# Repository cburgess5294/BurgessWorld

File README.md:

# BurgessWorld
A repository for documents related to BurgessWorld Custom Electronics Projects

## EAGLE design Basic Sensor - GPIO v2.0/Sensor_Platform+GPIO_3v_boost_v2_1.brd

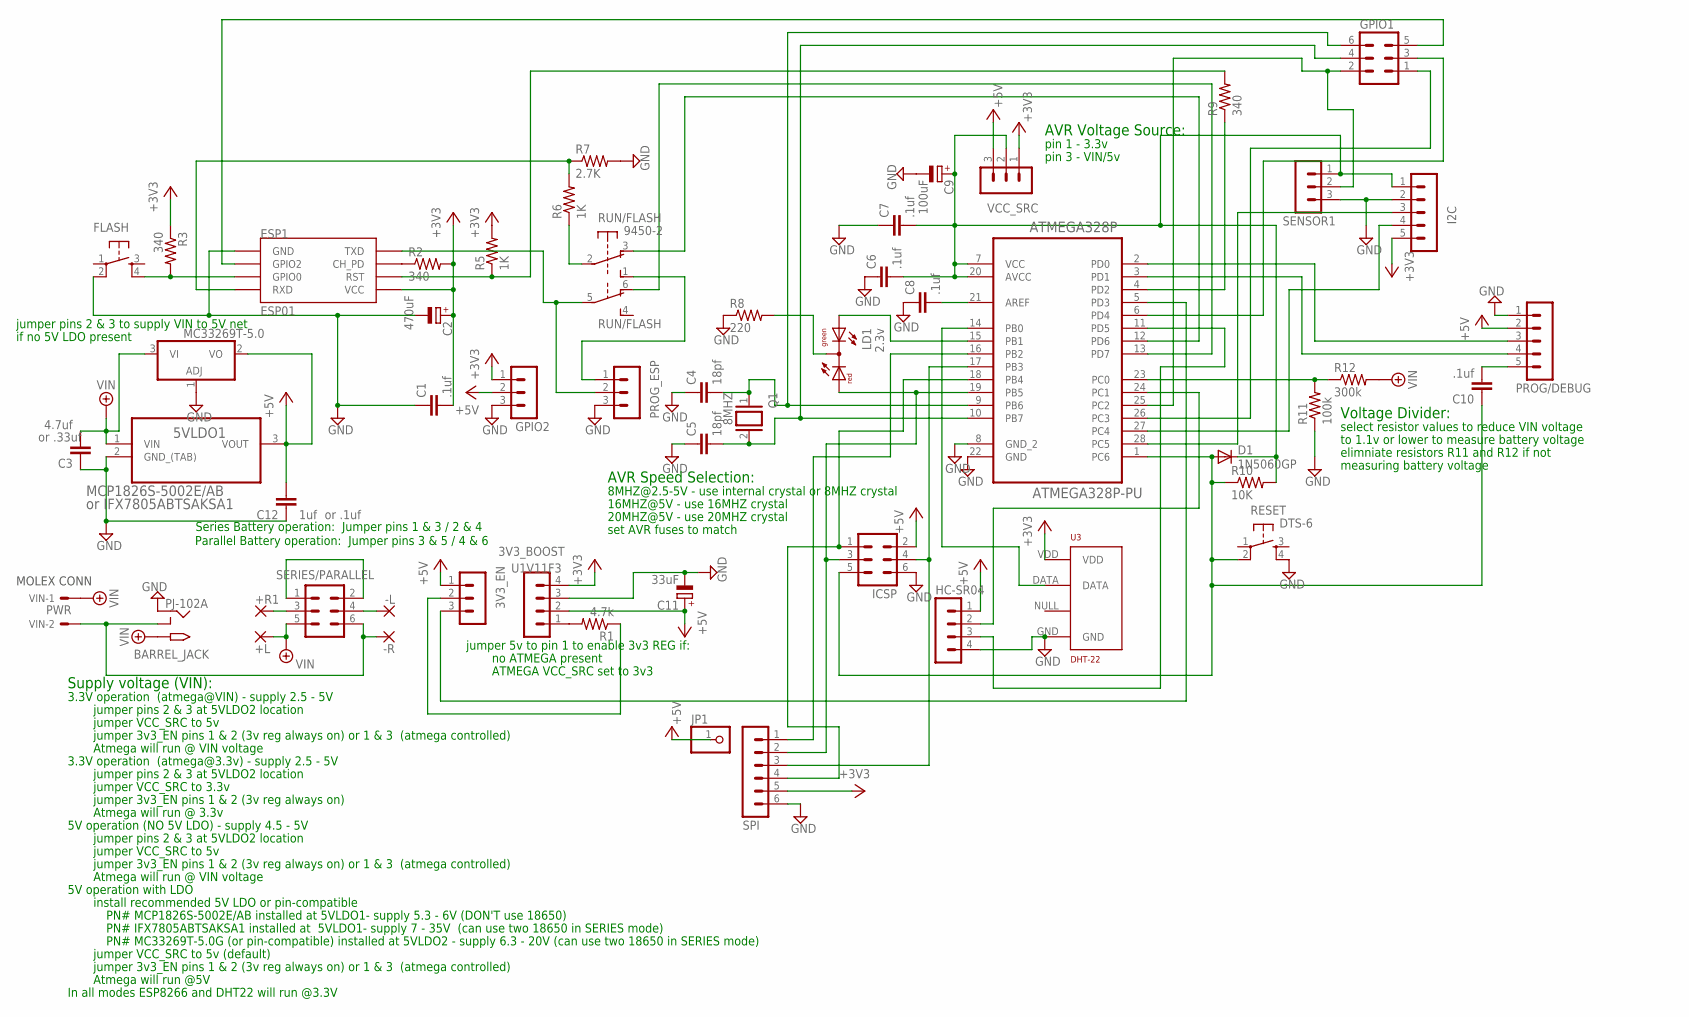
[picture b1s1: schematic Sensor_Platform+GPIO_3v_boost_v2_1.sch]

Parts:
3V3_BOOST: U1V11F3; MA04-1
3V3_EN: MA03-1
5VLDO1: MCP1826S-5002E/AB; TO254P482X1024X3124-3P
5VLDO2: MC33269T-5.0; TO220V
+L: WIREPADSMD2,54-5,08; SMD2,54-5,08
+R1: WIREPADSMD2,54-5,08; SMD2,54-5,08
-L: WIREPADSMD2,54-5,08; SMD2,54-5,08
-R: WIREPADSMD2,54-5,08; SMD2,54-5,08
ATMEGA328P: ATMEGA328P-PU; DIP254P762X457-28
BARREL_JACK: 2.1MMJACKTHM; PJ-102A
C1, C6, C7, C8, C10: .1uf; C2.5-2
C2: 470uF; E2,5-6E
C3: 4.7uf; C2.5-2
C4, C5: 18pf; C2.5-2
C9: 100uF; E2,5-6E
C11: 33uF; E2,5-6E
C12: 1uf; C2.5-2
D1: 1N5060GP; DO15-12
ESP1: ESP01
FLASH: DTS-6
GPIO1: MA03-2
GPIO2: MA03-1
HC-SR04: HC-SR04; MA04-1
I2C: MA05-1
ICSP: MA03-2
JP1: PINHD-1X1; 1X01
LD1: 2.3v; DUOLED-C-5MM
PROG/DEBUG: MA05-1
PROG_ESP: MA03-1
Q1: 8MHZ; QS
R1: 4.7k; 0207/7
R2, R3, R9: 340; 0207/7
R5, R6: 1K; 0207/7
R7: 2.7K; 0207/7
R8: 220; 0207/7
R10: 10K; 0207/7
R11: 100k; 0207/7
R12: 300k; 0207/7
RESET: DTS-6
RUN/FLASH: 9450-2
SENSOR1: MA03-1
SERIES/PARALLEL: MA03-2
SPI: MA06-1
U3: DHT-22; RHT03_DHT-22
VCC_SRC: MA03-1
VIN: PWR; 6410-02

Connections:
+3V3: 3V3_BOOST.4, C1.2, C2.+, ESP1.VCC, GPIO2.1, I2C.5, R2.2, R3.1, R5.2, SPI.5, U3.VDD, VCC_SRC.1
+4.1V: 5VLDO1.1 (VIN), 5VLDO2.3 (VI), +L.1, BARREL_JACK.TIP, C3.2, R12.2, SERIES/PARALLEL.5, VIN.1
+5V: 3V3_BOOST.2, 3V3_EN.1, 5VLDO1.3 (VOUT), 5VLDO2.2 (VO), C11.+, C12.2, GPIO2.2, HC-SR04.1, ICSP.2, JP1.1, PROG/DEBUG.2, VCC_SRC.3
GND: 3V3_BOOST.3, 5VLDO1.2 (GND_(TAB)), 5VLDO2.1 (ADJ), ATMEGA328P.8 (GND_2), ATMEGA328P.22 (GND), BARREL_JACK.RING, C1.1, C2.-, C3.1, C4.1, C5.1, C6.1, C7.1, C8.1, C9.-, C11.-, C12.1, ESP1.GND, FLASH.2, GPIO2.3, HC-SR04.4, I2C.2, ICSP.6, PROG/DEBUG.1, PROG_ESP.3, R7.2, R8.1, R11.1, RESET.4, SENSOR1.3, SPI.6, U3.GND
unnamed: ATMEGA328P.23 (PC0), R11.2, R12.1
unnamed: ESP1.GPIO0, FLASH.4, R3.2
unnamed: ATMEGA328P.26 (PC3), GPIO1.1
unnamed: ESP1.RST, R5.1, R9.2
unnamed: ATMEGA328P.4 (PD2), R9.1
unnamed: 3V3_BOOST.1, R1.2
unnamed: ESP1.GPIO2, GPIO1.5
unnamed: ATMEGA328P.15 (PB1), LD1.AX (AG)
unnamed: ATMEGA328P.19 (PB5), ICSP.3, LD1.AR, SPI.2
unnamed: ATMEGA328P.6 (PD4), GPIO1.3
unnamed: ATMEGA328P.7 (VCC), ATMEGA328P.20 (AVCC), C6.2, C7.2, C9.+, D1.C, I2C.1, R10.2, SENSOR1.1, VCC_SRC.2
unnamed: ATMEGA328P.12 (PD6), RUN/FLASH.3 (O)
unnamed: ATMEGA328P.13 (PD7), RUN/FLASH.6 (O)
unnamed: ATMEGA328P.21 (AREF), C8.2
unnamed: ESP1.RX (RXD), R6.2, R7.1
unnamed: ESP1.TX (TXD), PROG_ESP.2, RUN/FLASH.5
unnamed: ATMEGA328P.2 (PD0), PROG/DEBUG.3
unnamed: ATMEGA328P.3 (PD1), PROG/DEBUG.4
unnamed: 3V3_EN.3, ATMEGA328P.5 (PD3)
unnamed: C10.2, PROG/DEBUG.5
unnamed: ESP1.CH_PD, R2.1
unnamed: ATMEGA328P.17 (PB3), ICSP.4, SPI.3
unnamed: ATMEGA328P.14 (PB0), U3.DATA
unnamed: ATMEGA328P.18 (PB4), ICSP.1, SPI.4
unnamed: ATMEGA328P.9 (PB6), C4.2, GPIO1.6, Q1.1
unnamed: ATMEGA328P.10 (PB7), C5.2, GPIO1.4, Q1.2
unnamed: R6.1, RUN/FLASH.2
unnamed: ATMEGA328P.1 (PC6), C10.1, D1.A, ICSP.5, R10.1, RESET.2
unnamed: LD1.C, R8.2
unnamed: 3V3_EN.2, R1.1
unnamed: ATMEGA328P.28 (PC5), I2C.3
unnamed: PROG_ESP.1, RUN/FLASH.1 (S)
unnamed: ATMEGA328P.27 (PC4), I2C.4
unnamed: ATMEGA328P.25 (PC2), GPIO1.2, SENSOR1.2
unnamed: +R1.1, SERIES/PARALLEL.3
unnamed: -R.1, BARREL_JACK.RING_SW, SERIES/PARALLEL.6, VIN.2
unnamed: -L.1, SERIES/PARALLEL.4
unnamed: SERIES/PARALLEL.1, SERIES/PARALLEL.2
unnamed: ATMEGA328P.11 (PD5), HC-SR04.3
unnamed: ATMEGA328P.24 (PC1), HC-SR04.2
unnamed: ATMEGA328P.16 (PB2), SPI.1

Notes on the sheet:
jumper 5v to pin 1 to enable 3v3 REG if:
no ATMEGA present
jumper pins 2 & 3 to supply VIN to 5V net
if no 5V LDO present
AVR Speed Selection:
set AVR fuses to match
8MHZ@2.5-5V - use internal crystal or 8MHZ crystal
16MHZ@5V - use 16MHZ crystal
20MHZ@5V - use 20MHZ crystal
5V operation (NO 5V LDO) - supply 4.5 - 5V
install recommended 5V LDO or pin-compatible
3.3V operation (atmega@VIN) - supply 2.5 - 5V
Supply voltage (VIN):
Atmega will run @ VIN voltage
jumper pins 2 & 3 at 5VLDO2 location
5V operation with LDO
select resistor values to reduce VIN voltage
to 1.1v or lower to measure battery voltage
elimniate resistors R11 and R12 if not
measuring battery voltage
Voltage Divider:
AVR Voltage Source:
pin 1 - 3.3v
pin 3 - VIN/5v
ATMEGA VCC_SRC set to 3v3
jumper VCC_SRC to 3.3v
Atmega will run @ 3.3v
jumper VCC_SRC to 5v
3.3V operation (atmega@3.3v) - supply 2.5 - 5V
jumper 3v3_EN pins 1 & 2 (3v reg always on)
jumper 3v3_EN pins 1 & 2 (3v reg always on) or 1 & 3 (atmega controlled)
Atmega will run @5V
In all modes ESP8266 and DHT22 will run @3.3V
jumper VCC_SRC to 5v (default)
or IFX7805ABTSAKSA1
or .1uf
or .33uf
PN# IFX7805ABTSAKSA1 installed at 5VLDO1- supply 7 - 35V (can use two 18650 in SERIES mode)
PN# MC33269T-5.0G (or pin-compatible) installed at 5VLDO2 - supply 6.3 - 20V (can use two 18650 in SERIES mode)
PN# MCP1826S-5002E/AB installed at 5VLDO1- supply 5.3 - 6V (DON'T use 18650)

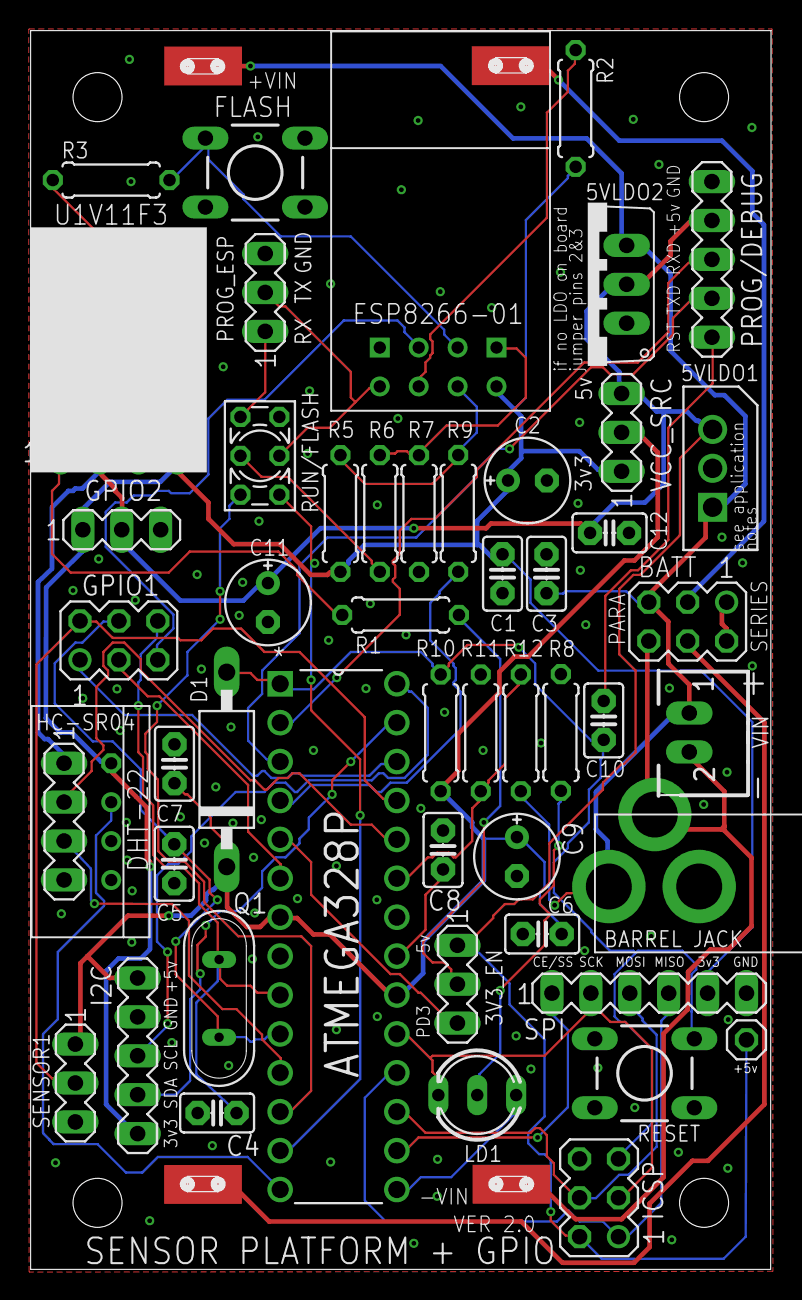
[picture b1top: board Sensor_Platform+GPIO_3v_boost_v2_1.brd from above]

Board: 2 copper layers, 47.9 x 80.5 mm, 54 parts (0 on the bottom side), 45 nets.

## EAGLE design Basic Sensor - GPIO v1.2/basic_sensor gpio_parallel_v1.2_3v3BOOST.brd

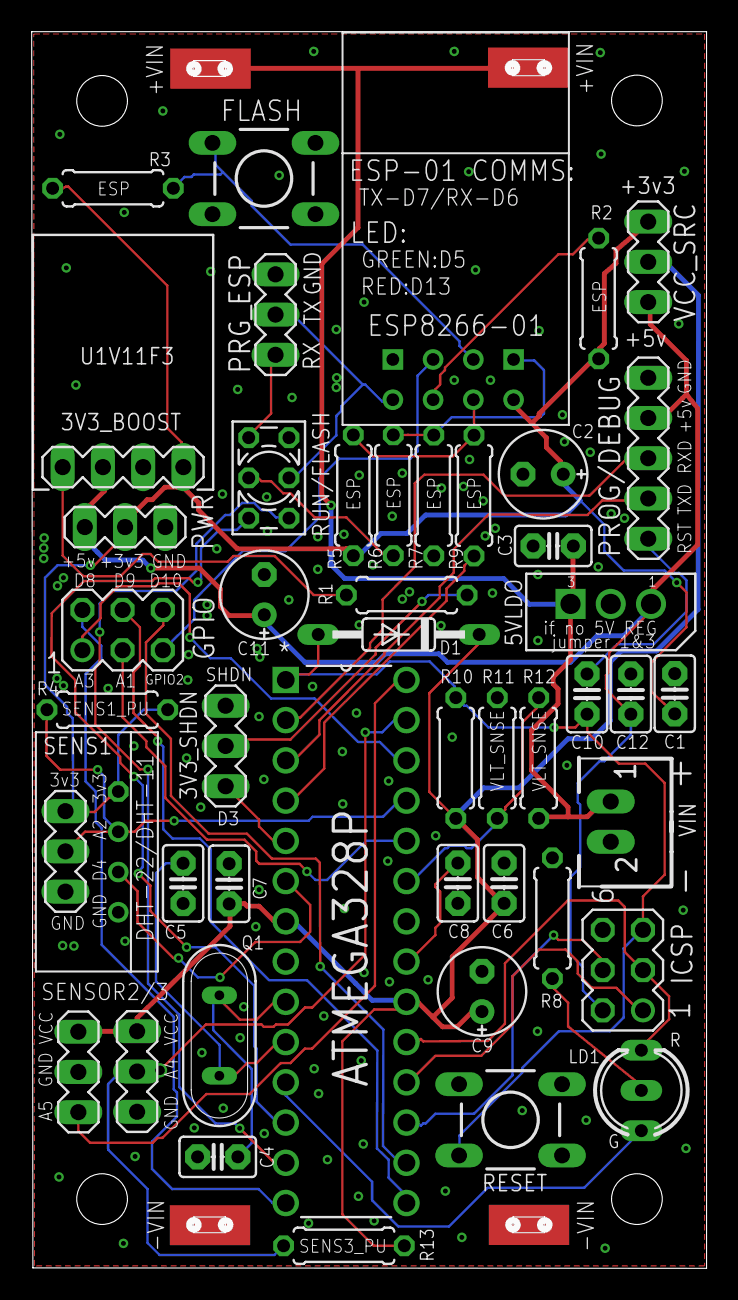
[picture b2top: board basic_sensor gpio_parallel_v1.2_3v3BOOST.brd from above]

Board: 2 copper layers, 42.2 x 77.6 mm, 51 parts (0 on the bottom side), 41 nets.

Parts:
3V3_BOOST: POLOLU-U1V11F3; MA04-1
3V3_SHDN: MA03-1
5VLDO: MCP1826S-5002E/AB; TO254P482X1024X3124-3P
+L: WIREPADSMD2,54-5,08; SMD2,54-5,08
+R: WIREPADSMD2,54-5,08; SMD2,54-5,08
-L: WIREPADSMD2,54-5,08; SMD2,54-5,08
-R: WIREPADSMD2,54-5,08; SMD2,54-5,08
ATMEGA328P: ATMEGA328P-PU; DIP254P762X457-28
C1, C6, C7, C8, C10: .1uf; C2.5-2
C2: 470uF; E2,5-6E
C3: 4.7uf; C2.5-2
C4, C5: 18pf; C2.5-2
C9: 100uF; E2,5-6E
C11: 33uF; E2,5-6E
C12: 1uf; C2.5-2
D1: 1N4148DO35-10; DO35-10
DHT-22/DHT-11: DHT-22; RHT03_DHT-22
ESP1: ESP01
FLASH: DTS-6
GPIO: MA03-2
ICSP: MA03-2
LD1: 2.3v; DUOLED-C-5MM
PRG_ESP: MA03-1
PROG/DEBUG: MA05-1
PWR: MA03-1
Q1: 8MHZ; QS
R1: 4.7k; 0207/7
R2, R3: 340; 0207/7
R4, R8: 220; 0207/7
R5, R6: 1K; 0207/7
R7: 2.7K; 0207/7
R9: 0 ohm; 0207/7
R10: 10K; 0207/7
R11: 100k; 0207/7
R12: 300k; 0207/7
R13: 4.7; 0207/7
RESET: DTS-6
RUN/FLASH: 9450-2
SENS1: MA03-1
SENSOR2, SENSOR3: MA03-1
VCC_SRC: MA03-1
VIN: PWR; 6410-02

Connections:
3V3_SDN_JMP: 3V3_SHDN.2, R1.1
3V3_SHUTDOWN: 3V3_BOOST.1, R1.2
+3V3: 3V3_BOOST.4, C1.2, C2.+, DHT-22/DHT-11.VDD, ESP1.VCC, PWR.2, R2.2, R3.1, R4.2, R5.2, SENS1.1, VCC_SRC.1
+4.1V: 5VLDO.1, +L.1, +R.1, C3.2, R12.2, VIN.1
+5V: 3V3_BOOST.2, 5VLDO.3, C11.+, C12.2, ICSP.2, PROG/DEBUG.2, PWR.1, VCC_SRC.3
ESP-RXD-SW: PRG_ESP.1, RUN/FLASH.1
ESP_CH_PD: ESP1.CH_PD, R2.1
ESP_GPIO0: ESP1.GPIO0, FLASH.4, R3.2
ESP_GPIO2: ESP1.GPIO2, GPIO.5
ESP_RST: ESP1.RST, R5.1, R9.2
ESP_RXD: ESP1.RX, R6.2, R7.1
ESP_RXD_VD: R6.1, RUN/FLASH.2
ESP_TXD: ESP1.TX, PRG_ESP.2, RUN/FLASH.5
GND: 3V3_BOOST.3, 3V3_SHDN.1, 5VLDO.2, -L.1, -R.1, ATMEGA328P.8, ATMEGA328P.22, C1.1, C2.-, C3.1, C4.1, C5.1, C6.1, C7.1, C8.1, C9.-, C11.-, C12.1, DHT-22/DHT-11.GND, ESP1.GND, FLASH.2, ICSP.6, PRG_ESP.3, PROG/DEBUG.1, PWR.3, R7.2, R8.1, R11.1, RESET.3, RESET.4, SENS1.3, SENSOR2.2, SENSOR3.3, VIN.2
MISO/D12: ATMEGA328P.18, ICSP.1
MOSI/D11: ATMEGA328P.17, ICSP.4
unnamed: ATMEGA328P.21, C8.2
unnamed: C10.2, PROG/DEBUG.5
unnamed: LD1.C, R8.2
PB0/D8: ATMEGA328P.14, GPIO.2
PB1/D9: ATMEGA328P.15, GPIO.4
PB2/D10: ATMEGA328P.16, GPIO.6
PC0/D14/A0: ATMEGA328P.23, R11.2, R12.1
PC1/D15/A1: ATMEGA328P.24, GPIO.3
PC2/D16/A2: ATMEGA328P.25, DHT-22/DHT-11.DATA, R4.1, SENS1.2
PC3/D17/A3: ATMEGA328P.26, GPIO.1
PC4/D18/A4: ATMEGA328P.27, R13.1, SENSOR3.2
PC5/D19/A5: ATMEGA328P.28, SENSOR2.3
PD2/D2: ATMEGA328P.4, R9.1
PD3/D3: 3V3_SHDN.3, ATMEGA328P.5
PD4/D4: ATMEGA328P.6, DHT-22/DHT-11.NULL
PD5/D5: ATMEGA328P.11, LD1.AX
PD6/D6: ATMEGA328P.12, RUN/FLASH.3
PD7/D7: ATMEGA328P.13, RUN/FLASH.6
RESET: ATMEGA328P.1, C10.1, D1.A, ICSP.5, R10.1, RESET.2
RXD: ATMEGA328P.2, PROG/DEBUG.3
SCK/D13: ATMEGA328P.19, ICSP.3, LD1.AR
TXD: ATMEGA328P.3, PROG/DEBUG.4
VCC_SRC: ATMEGA328P.7, ATMEGA328P.20, C6.2, C7.2, C9.+, D1.C, R10.2, R13.2, SENSOR2.1, SENSOR3.1, VCC_SRC.2
XAL2/PB7: ATMEGA328P.10, C5.2, Q1.2
XTAL1/PB6: ATMEGA328P.9, C4.2, Q1.1

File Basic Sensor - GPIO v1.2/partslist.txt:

Partlist

Exported from basic_sensor gpio_parallel_v1.2_3v3BOOST.brd at 5/7/2017 8:17 PM

EAGLE Version 8.1.1 Copyright (c) 1988-2017 Autodesk, Inc.

Assembly variant: 

Part          Value               Package                Library                        Position (mil)        Orientation

3V3_BOOST     POLOLU-U1V11F3      4-PIN MODULE           my-custom-lib                  (466 2021)            R0
3V3_SHDN                          MA03-1                 my-custom-lib                  (721 1328)            R270
(OPT1)5VLDO   MCP1826S-5002E/AB   TO254P482X1024X3124-3P Microchip_By_element14_Batch_1 (1778 1642)           R0
(OPT2)5VBOOST U3V12F5		  3-PIN MODULE
(OPT3)5VBOOST S9V11F5		  3-PIN MODULE
ATMEGA328P    ATMEGA328P-PU       DIP254P762X457-28      Atmel_By_element14_Batch_1-00  (1170.37795 192.18898) R0
C1            .1uf                C2.5-2                 capacitor-wima                 (1837.07087 1457.88189) R270
C2            470uF               E2,5-6E                rcl                            (1509.88976 2003.37008) R180
C3            4.7uf               C2.5-2                 capacitor-wima                 (1535 1825)           R0
C4            18pf                C2.5-2                 capacitor-wima                 (701.32283 306.92126) R0
C5            18pf                C2.5-2                 capacitor-wima                 (615.25984 986.66142) R90
C6            .1uf                C2.5-2                 capacitor-wima                 (1413 987)            R270
C7            .1uf                C2.5-2                 capacitor-wima                 (729.74803 985.5748)  R270
C8            .1uf                C2.5-2                 capacitor-wima                 (1298 987)            R90
C9            100uF               E2,5-6E                rcl                            (1358 718)            R90
C10           .1uf                C2.5-2                 capacitor-wima                 (1619 1457)           R90
C11           33uF                E2,5-6E                rcl                            (817 1704)            R90
C12           1uf                 C2.5-2                 capacitor-wima                 (1728 1457)           R270
D1            1N4148DO35-10       DO35-10                diode                          (1151 1605)           R180
DHT-22/DHT-11 DHT-22              RHT03_DHT-22           RHT03_DHT-22_AM2302            (454.15748 1064.80315) R270
ESP1          ESP01               ESP01                  esp8266modules                 (1287.11024 2510.37008) R0
FLASH                             DTS-6                  switch-tact                    (816.25984 2738.11024) R180
GPIO                              MA03-2                 my-custom-lib                  (465 1616)            R0
ICSP                              MA03-2                 con-lstb                       (1708 771)            R90
LD1           2.3v                DUOLED-C-5MM           led                            (1754 472)            R90
PRG_ESP                           MA03-1                 my-custom-lib                  (845 2400)            R90
PROG/DEBUG                        MA05-1                 con-lstb                       (1771.11024 2043)     R270
PWR                               MA03-1                 my-custom-lib                  (471 1872)            R0
Q1            8MHZ                QS                     special                        (705.4252 608.44882)  R270
R1            4.7k                0207/7                 rcl                            (1171 1703)           R180
R2            340                 0207/7                 rcl                            (1648 2440)           R270
R3            340                 0207/7                 rcl                            (441 2713.88976)      R0
R4            220                 0207/7                 rcl                            (427 1418)            R0
R5            1K                  0207/7                 rcl                            (1038.30709 1950.88976) R270
R6            1K                  0207/7                 rcl                            (1137.62992 1950.96063) R90
R7            2.7K                0207/7                 rcl                            (1238.25197 1950.51969) R270
R8            220                 0207/7                 rcl                            (1533 900)            R270
R9            0 ohms              0207/7                 rcl                            (1338.18898 1950.1811) R90
R10           10K                 0207/7                 rcl                            (1293 1298)           R270
R11           100k                0207/7                 rcl                            (1396 1298)           R270
R12           300k                0207/7                 rcl                            (1499 1298)           R270
R13           4.7                 0207/7                 rcl                            (1015 86)             R0
RESET         DTS-6               DTS-6                  switch-tact                    (1429 399)            R180
RUN/FLASH     9450-2              9450-2                 switch-misc                    (828.34646 1994.15748) R270
SENS1                             MA03-1                 my-custom-lib                  (323 1066)            R270
SENSOR2                           MA03-1                 my-custom-lib                  (355 518)             R270
SENSOR3                           MA03-1                 my-custom-lib                  (501 519)             R270
VCC_SRC                           MA03-1                 my-custom-lib                  (1771 2531)           R270
VIN           MOLEX               6410-02                con-molex                      (1714 1140)           R90

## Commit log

2017-05-17 Create ThingSpeak_temperature_humidity_example.ino
    Example Arduino sketch to upload temperature and humidity data to a thingspeak.com channnel.
    This sketch is designed to be used with Basic and Advanced Sensor Boards sold by the BurgessWorld
    Custom Electronics Tindie store.
    You can modify this sketch for your purposes and use it with other boards as you see fit.
2017-09-21 Create temp
2018-03-30 Update temp
2018-05-04 Add files via upload
    Modified Library for the NodeMCU 12-Bit ADC Shield
2018-06-21 Create Welcome
2018-06-22 test
2018-06-22 Add python examples
2018-06-23 Add teensy spi example
2018-06-25 adding example directories
2018-06-25 adding readme file
2018-06-25 adding arduino example sketches
2018-06-28 Add existing file
2018-06-28 updated sketch
2018-06-28 add new python script
2018-06-30 updated python scripting
2018-07-11 Add files via upload
    version 1.1 of the sketch to conform to slightly different timing of newer AI Thinker firmware on the ESP8266
2018-07-30 adding MCP3208 example
2018-09-05 Add rpi_avr_i2c_SMBUS_example_v2.py
2018-09-05 changing example file names
2018-09-05 correcting test example python script
2018-09-05 removing superseded sketch
2018-09-05 uploading new sketch
2018-09-05 minor changes to sketches
2018-09-05 adding new i2c example
2018-09-07 Create project directory
2018-09-07 Add MCP32008 and EEPROM24 Example sketches
2018-09-07 Add EEPROM24 Library
2018-09-07 Add design files
2018-09-20 Upload BRD pdf file
2018-09-20 Upload SCH pdf file
2018-09-20 remove temp file
2019-02-17 Adding HS300x Examples
2019-02-17 renaming HS3003 files
2019-02-18 updating HS300x scripts
2019-02-22 modified zmod scripts
2019-02-22 modified zmod dir
2019-03-16 Adding MCP3008 Files
2019-03-16 revert MCP3008 change
2019-03-16 add MCP3008 examples
2019-05-02 Rename ESP32_Simple_Web_Motor_Control_v2.ino to Simple_Web_Motor_Control_v2.ino
2019-05-02 Rename Simple_Web_Motor_Control_v2.ino to Simple_Wifi_Motor_Interface_v2.ino
2019-09-01 added custom library
2019-09-01 change int to uint32_t to prevent overflow warning
2019-09-01 removed identifying info
2019-09-01 minor modification
    modified source library path and changed int to int32_t
2019-09-20 Added schematic and board file
2019-09-22 Added schematic and board files
2019-10-10 Create new
2019-12-08 Added design files for rev 3
2020-12-13 Add files via upload
    adding schematic and board files for rev2
2020-12-28 updating example scripts
2020-12-28 Updated logic test Arduino sketch
    added python logic test example
2020-12-28 modified avr_logic_test python script
2020-12-28 modify avr_logi_example
2020-12-28 updated welcome message
2021-02-02 who knows
2021-02-25 Create Using_The_MCP3208
2021-04-13 Add files via upload
    Example config gile GFP_MASTER.hex file can be uploaded to the BM83 along with the DSP and firmware hex files to enable single-output amplifier mode and battery charging.
2021-08-04 Delete _20A_Motor_Controller_Example_v1.ino
    removing old example sketch
2021-08-04 adding updated example sketch
2022-01-08 Create Python_Example_1
2022-01-08 Create Shift_Pi_Python_example
2022-01-12 add jetson nano example
2022-01-12 update jetson nano example
2024-12-19 Delete BM83/BM83_DEV_Board_v13_SCH.pdf
    remove old version
2024-12-19 Add files via upload
    update schematic files for DEV board
